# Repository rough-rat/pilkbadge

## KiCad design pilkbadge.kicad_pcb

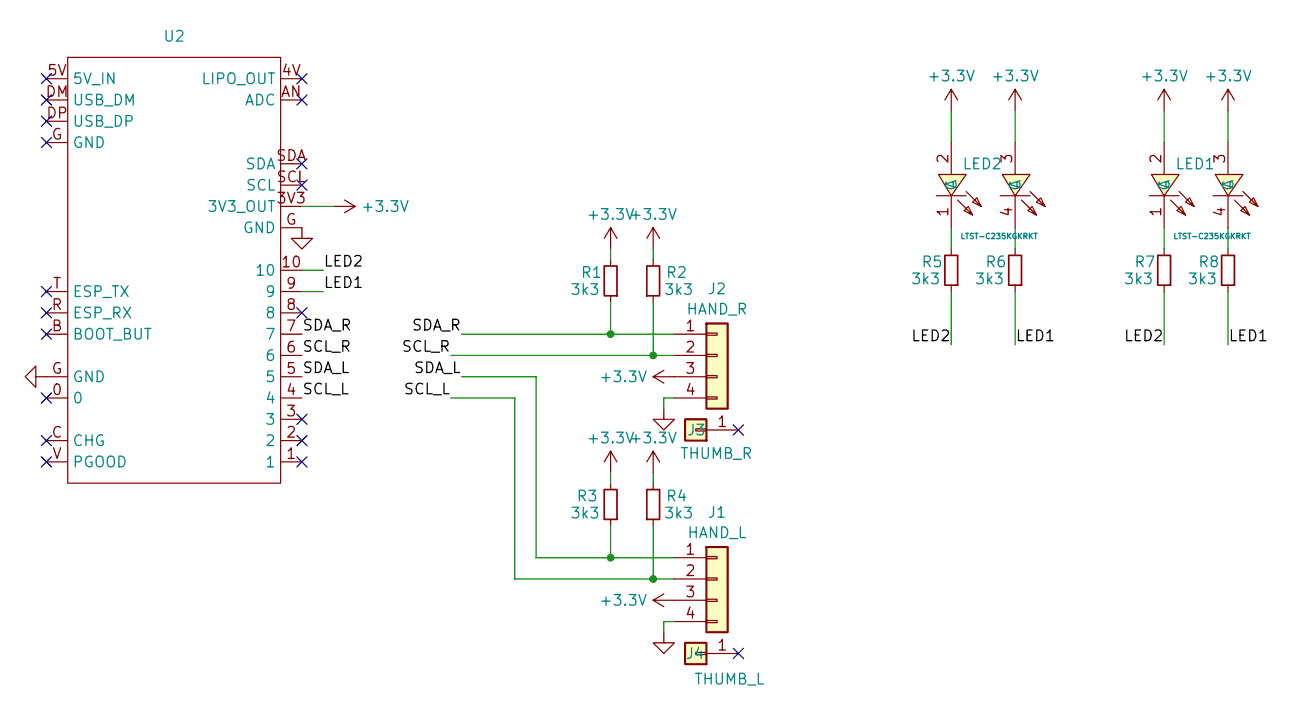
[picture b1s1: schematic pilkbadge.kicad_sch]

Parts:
J1: HAND_L; Neko_hands
J2: HAND_R; Neko_hands
J3: THUMB_R; PinHeader_1x01_P2.54mm_Vertical
J4: THUMB_L; PinHeader_1x01_P2.54mm_Vertical
LED1, LED2: LTST-C235KGKRKT; LED-SMD_LTST-C235KGKRKT; LCSC Part C125110
R1, R2, R3, R4, R5, R6, R7, R8: 3k3; R_0603_1608Metric_Pad0.98x0.95mm_HandSolder
U2: pilkbrain4

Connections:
+3.3V: J1.3, J2.3, LED1.2 (A), LED1.3 (A), LED2.2 (A), LED2.3 (A), R1.2, R2.2, R3.2, R4.2, U2.3V3 (3V3_OUT)
/LED1: R6.1, R8.1, U2.9
/LED2: R5.1, R7.1, U2.10
/SCL_L: J1.2, R4.1, U2.4
/SCL_R: J2.2, R2.1, U2.6
/SDA_L: J1.1, R3.1, U2.5
/SDA_R: J2.1, R1.1, U2.7
GND: J1.4, J2.4, U2.G (GND)
unnamed: LED1.1 (C), R7.2
unnamed: LED1.4 (C), R8.2
unnamed: LED2.1 (C), R5.2
unnamed: LED2.4 (C), R6.2

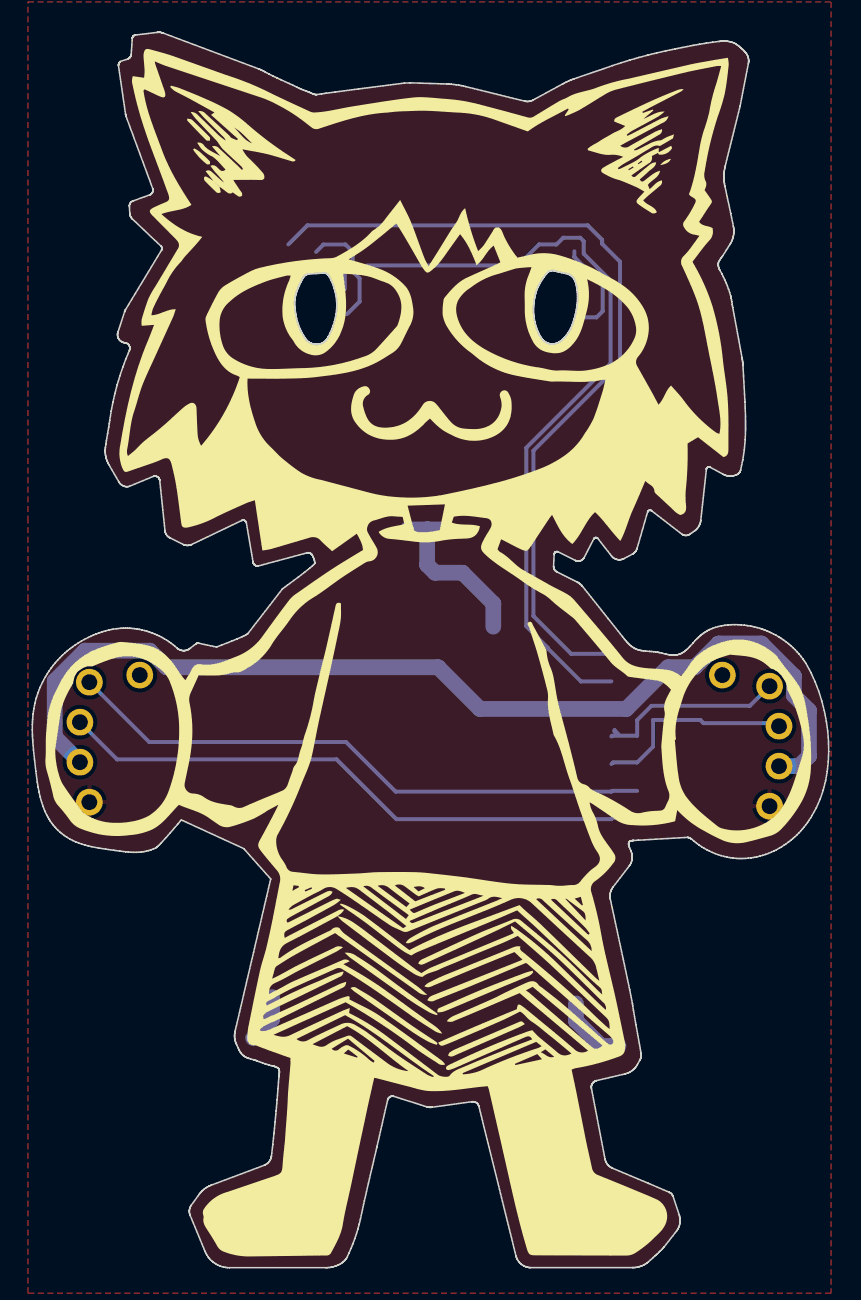
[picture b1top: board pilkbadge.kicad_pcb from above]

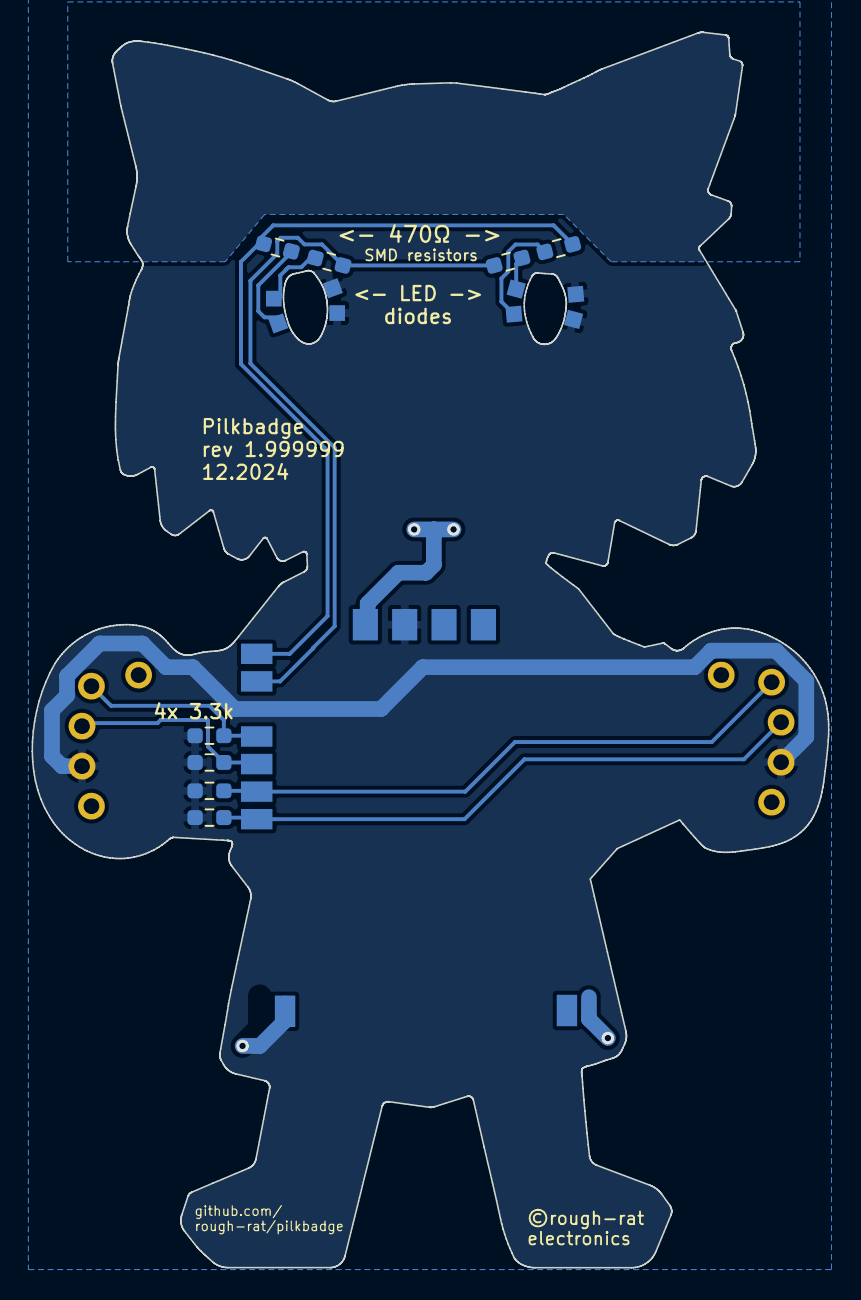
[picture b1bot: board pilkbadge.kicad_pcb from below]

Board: 2 copper layers, 50.6 x 78.5 mm, 15 parts (14 on the bottom side), 12 nets.

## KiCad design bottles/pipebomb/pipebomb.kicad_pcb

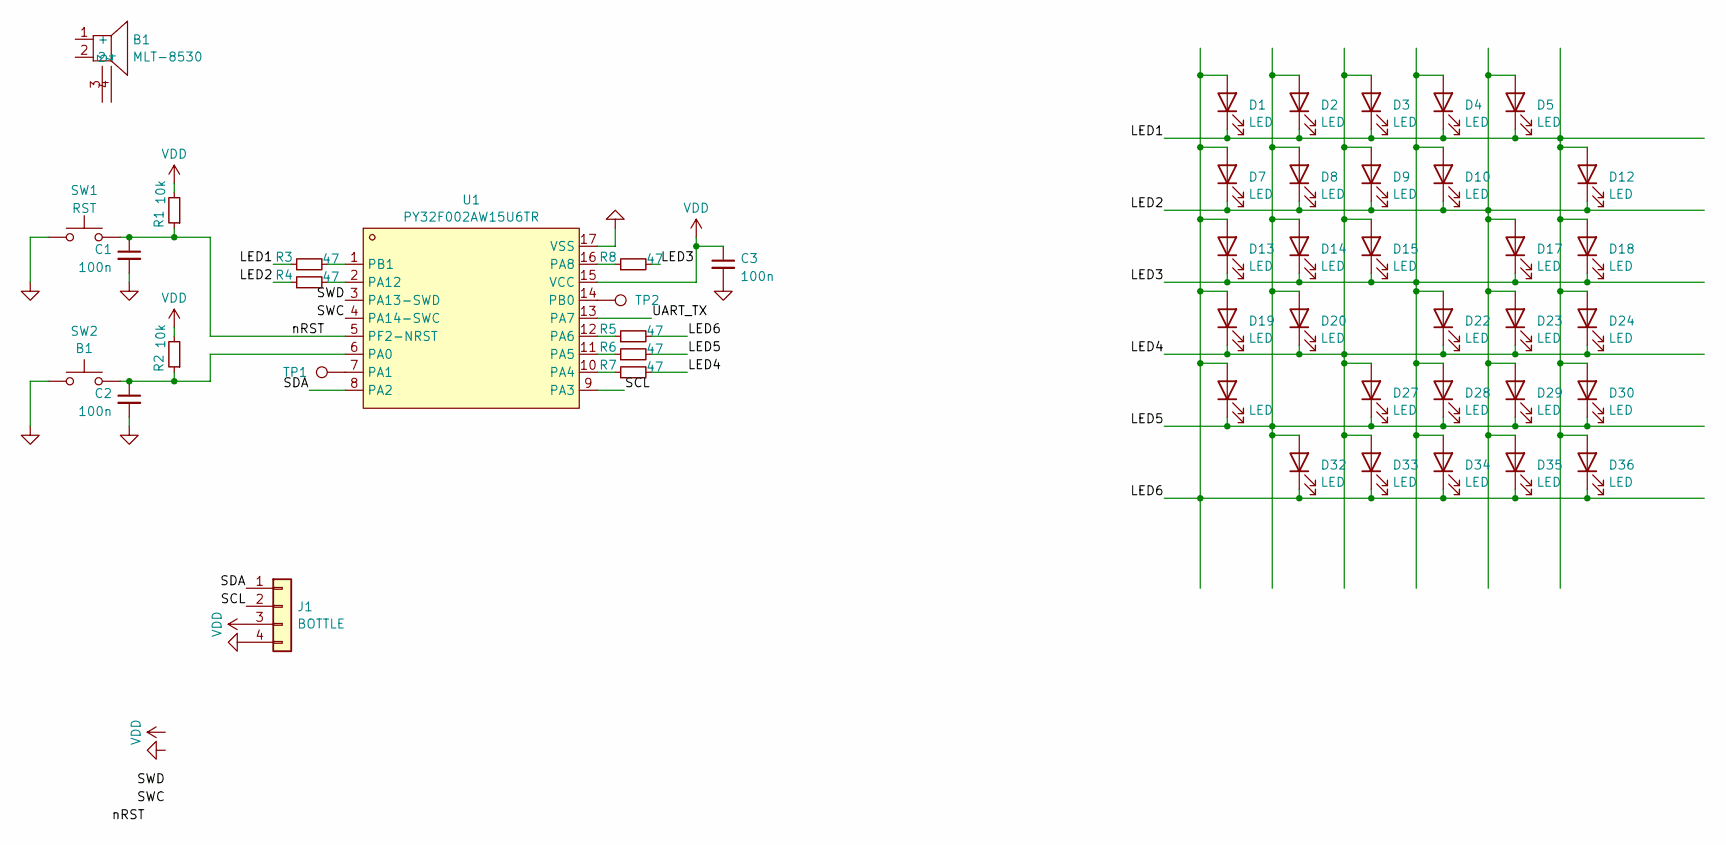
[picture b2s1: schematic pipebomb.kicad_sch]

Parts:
B1: MLT-8530; BUZ-SMD_4P-L8.5-W8.5-P8.50-BR
C1, C2, C3: 100n; C_0402_1005Metric; LCSC C307331
D1, D2, D3, D4, D5, D7, D8, D9, D10, D12, D13, D14, D15, D17, D18, D19, D20, D22, D23, D24, D25, D27, D28, D29, D30, D32, D33, D34, D35, D36: LED; LED_0402_1005Metric
J1: BOTTLE; PinHeader_1x04_P2.54mm_Vertical
R1, R2: 10k; R_0402_1005Metric; LCSC C25744
R3, R4, R5, R6, R7, R8: 47; R_0402_1005Metric; LCSC C25744
SW1: RST; SW_SPST_FSMSM; LCSC DNP
SW2: B1; SW_SPST_FSMSM; LCSC DNP
TP1, TP2: IOPAD; TestPoint_Pad_D1.0mm; LCSC DNP
U1: PY32F002AW15U6TR; TQFN-16_L3.0-W3.0-P0.50-BL-EP1.7; LCSC Part C5291740

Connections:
/LED1: D1.1 (K), D2.1 (K), D3.1 (K), D4.1 (K), D5.1 (K), D12.2 (A), D18.2 (A), D24.2 (A), D30.2 (A), D36.2 (A), R3.1
/LED2: D5.2 (A), D7.1 (K), D8.1 (K), D9.1 (K), D10.1 (K), D12.1 (K), D17.2 (A), D23.2 (A), D29.2 (A), D35.2 (A), R4.1
/LED3: D4.2 (A), D10.2 (A), D13.1 (K), D14.1 (K), D15.1 (K), D17.1 (K), D18.1 (K), D22.2 (A), D28.2 (A), D34.2 (A), R8.2
/LED4: D3.2 (A), D9.2 (A), D15.2 (A), D19.1 (K), D20.1 (K), D22.1 (K), D23.1 (K), D24.1 (K), D27.2 (A), D33.2 (A), R7.2
/LED5: D2.2 (A), D8.2 (A), D14.2 (A), D20.2 (A), D25.1 (K), D27.1 (K), D28.1 (K), D29.1 (K), D30.1 (K), D32.2 (A), R6.2
/LED6: D1.2 (A), D7.2 (A), D13.2 (A), D19.2 (A), D25.2 (A), D32.1 (K), D33.1 (K), D34.1 (K), D35.1 (K), D36.1 (K), R5.2
/SCL: J1.2, U1.9 (PA3)
/SDA: J1.1, U1.8 (PA2)
/SWC: U1.4 (PA14-SWC)
/SWD: U1.3 (PA13-SWD)
/UART_TX: U1.13 (PA7)
/nRST: C1.1, R1.1, SW1.2, U1.5 (PF2-NRST)
GND: C1.2, C2.2, C3.2, J1.4, SW1.1, SW2.1, U1.17 (VSS)
unnamed: C2.1, R2.1, SW2.2, U1.6 (PA0)
unnamed: TP1.1, U1.7 (PA1)
unnamed: R7.1, U1.10 (PA4)
unnamed: R6.1, U1.11 (PA5)
unnamed: R5.1, U1.12 (PA6)
unnamed: R8.1, U1.16 (PA8)
unnamed: R4.2, U1.2 (PA12)
unnamed: TP2.1, U1.14 (PB0)
unnamed: R3.2, U1.1 (PB1)
VDD: C3.1, J1.3, R1.2, R2.2, U1.15 (VCC)

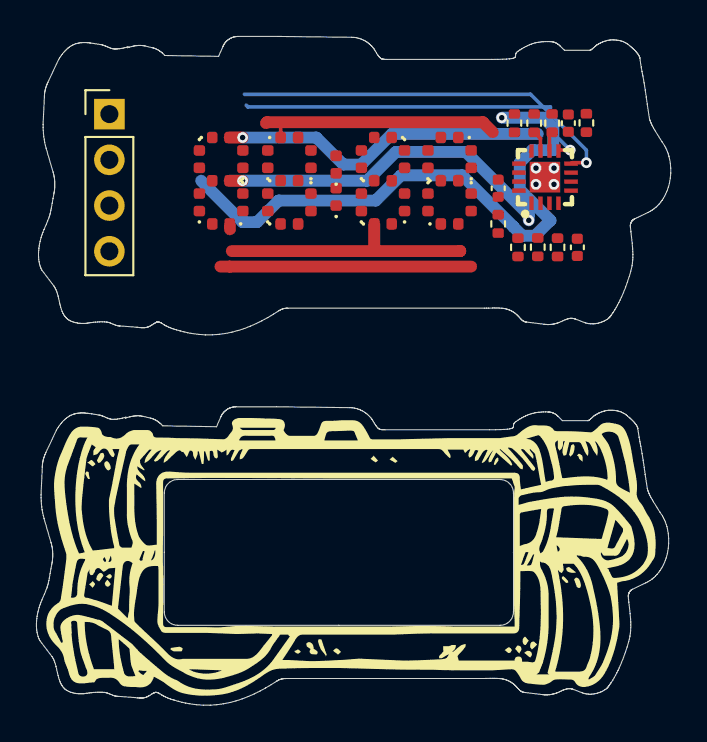
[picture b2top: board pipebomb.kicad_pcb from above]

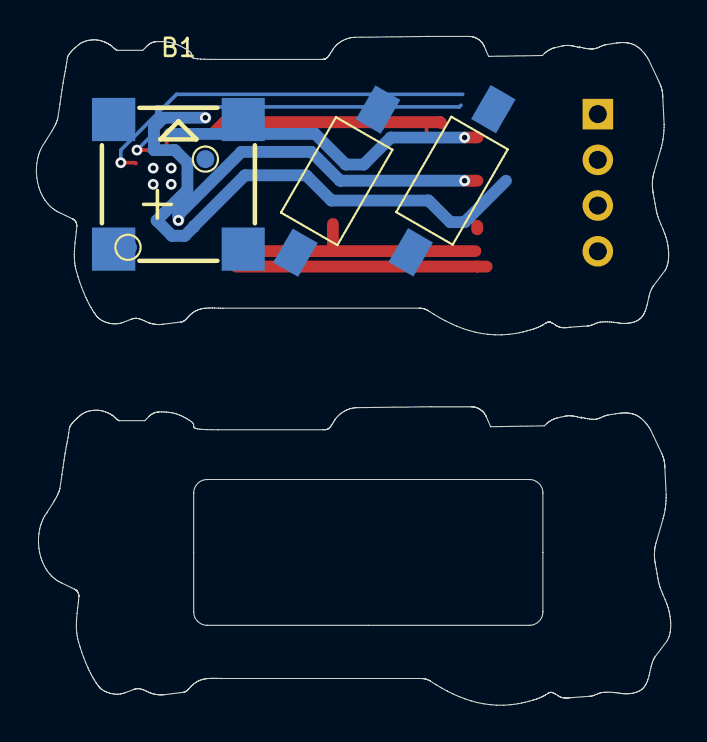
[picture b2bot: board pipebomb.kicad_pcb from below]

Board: 2 copper layers, 35.1 x 16.6 mm, 48 parts (5 on the bottom side), 20 nets.

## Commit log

2024-07-13 add pipebomb progress
2024-09-29 smart(dumb) neko
2024-09-29 PIPEBOMB
2024-09-29 failed panels (add vcut to gerbers next time)
2024-10-27 adapt to pilkbrain
2024-11-21 move bottles to another repo
2024-11-21 order: golden neko / pilkbrain tests
2024-11-21 1.99 order
2024-12-09 pilkbrain v4

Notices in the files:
pilkbadge.kicad_pcb:
©rough-rat
Artwork © 2024 by Ewa Kielska
licensed under CC BY-NC-ND 4.0
licensed under CERN-OHL-W
